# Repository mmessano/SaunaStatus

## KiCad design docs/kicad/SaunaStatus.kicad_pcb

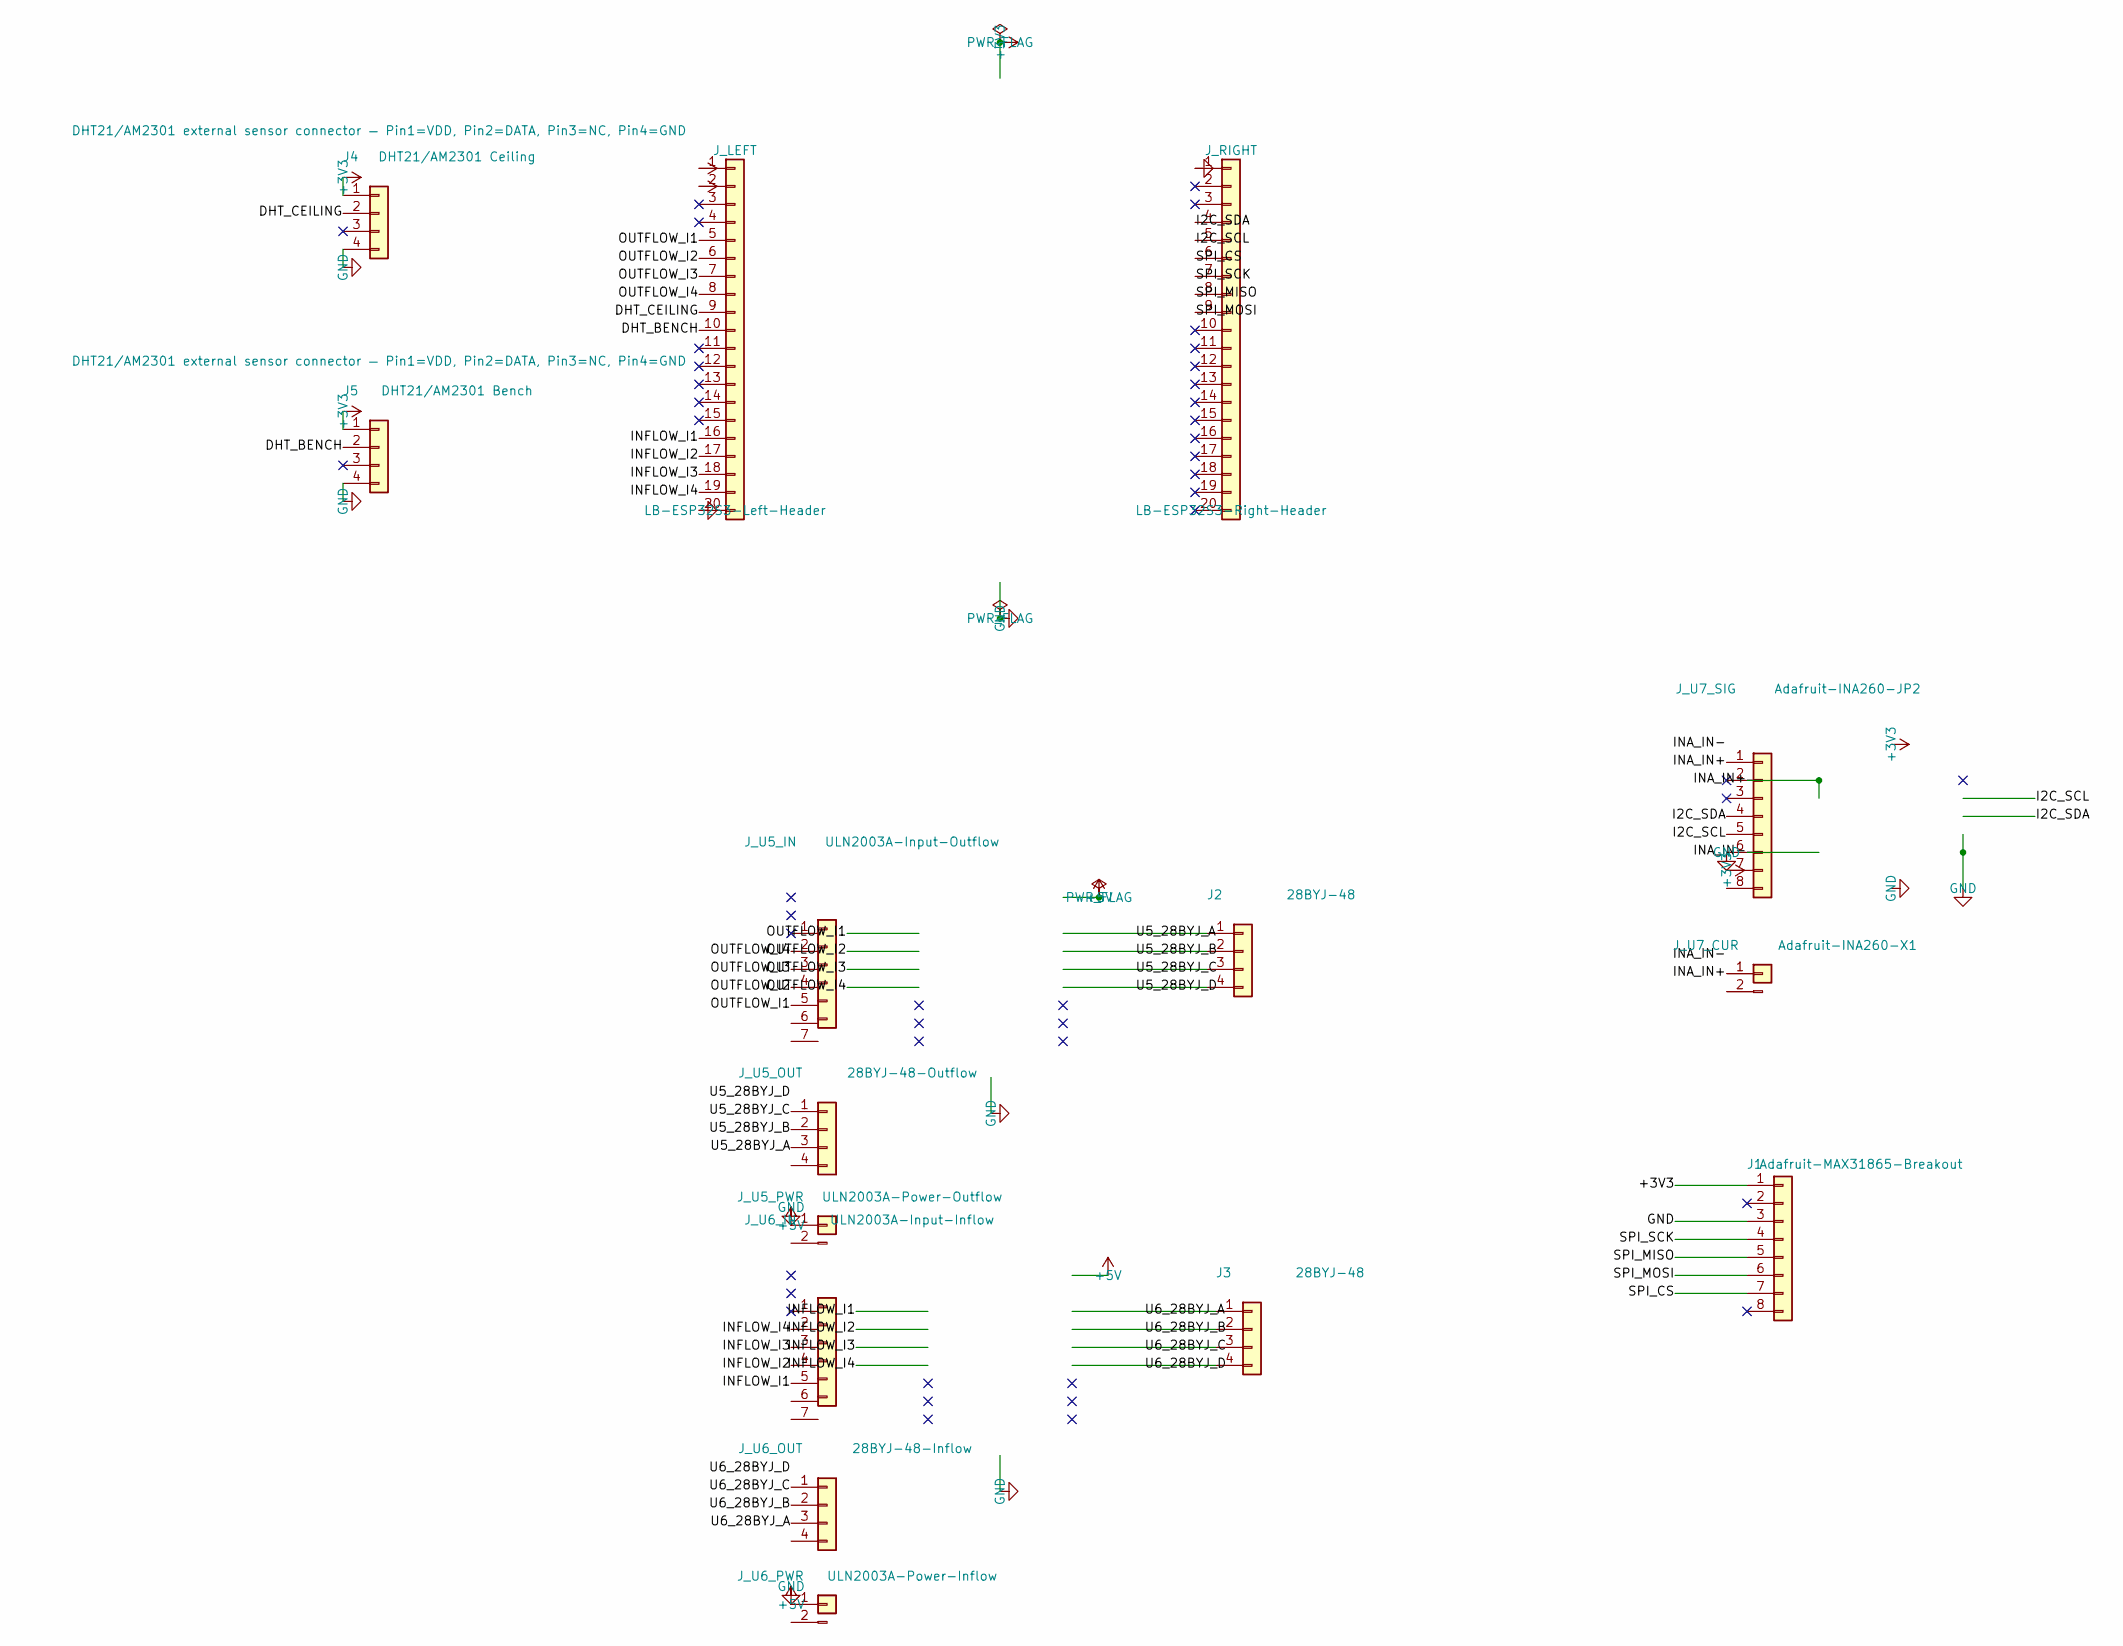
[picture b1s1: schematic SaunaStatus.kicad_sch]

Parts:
J1: Adafruit-MAX31865-Breakout; PinHeader_1x08_P2.54mm_Vertical
J2, J3: 28BYJ-48; PinHeader_1x04_P2.54mm_Vertical
J4: DHT21/AM2301 Ceiling; PinHeader_1x04_P2.54mm_Vertical
J5: DHT21/AM2301 Bench; PinHeader_1x04_P2.54mm_Vertical
J_LEFT: LB-ESP32S3-Left-Header; PinHeader_1x20_P2.54mm_Vertical
J_RIGHT: LB-ESP32S3-Right-Header; PinHeader_1x20_P2.54mm_Vertical
J_U5_IN: ULN2003A-Input-Outflow; PinHeader_1x07_P2.54mm_Vertical
J_U5_OUT: 28BYJ-48-Outflow; PinHeader_1x04_P2.54mm_Vertical
J_U5_PWR: ULN2003A-Power-Outflow; PinHeader_1x02_P2.54mm_Vertical
J_U6_IN: ULN2003A-Input-Inflow; PinHeader_1x07_P2.54mm_Vertical
J_U6_OUT: 28BYJ-48-Inflow; PinHeader_1x04_P2.54mm_Vertical
J_U6_PWR: ULN2003A-Power-Inflow; PinHeader_1x02_P2.54mm_Vertical
J_U7_CUR: Adafruit-INA260-X1; PinHeader_1x02_P2.54mm_Vertical
J_U7_SIG: Adafruit-INA260-JP2; PinHeader_1x08_P2.54mm_Vertical

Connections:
+3V3: J1.1, J4.1, J5.1, J_LEFT.1, J_LEFT.2, J_U7_SIG.7
+5V: J_U5_PWR.1, J_U6_PWR.1
/DHT_BENCH: J5.2, J_LEFT.10; also elsewhere on the board
/DHT_CEILING: J4.2, J_LEFT.9; also elsewhere on the board
/I2C_SCL: J_RIGHT.5, J_U7_SIG.5; also elsewhere on the board
/I2C_SDA: J_RIGHT.4, J_U7_SIG.4; also elsewhere on the board
/INA_IN+: J_U7_CUR.1, J_U7_SIG.1
/INFLOW_I1: J_LEFT.16, J_U6_IN.5; also elsewhere on the board
/INFLOW_I2: J_LEFT.17, J_U6_IN.4; also elsewhere on the board
/INFLOW_I3: J_LEFT.18, J_U6_IN.3; also elsewhere on the board
/INFLOW_I4: J_LEFT.19, J_U6_IN.2; also elsewhere on the board
/OUTFLOW_I1: J_LEFT.5, J_U5_IN.5; also elsewhere on the board
/OUTFLOW_I2: J_LEFT.6, J_U5_IN.4; also elsewhere on the board
/OUTFLOW_I3: J_LEFT.7, J_U5_IN.3; also elsewhere on the board
/OUTFLOW_I4: J_LEFT.8, J_U5_IN.2; also elsewhere on the board
/SPI_CS: J1.7, J_RIGHT.6; also elsewhere on the board
/SPI_MISO: J1.5, J_RIGHT.8; also elsewhere on the board
/SPI_MOSI: J1.6, J_RIGHT.9; also elsewhere on the board
/SPI_SCK: J1.4, J_RIGHT.7; also elsewhere on the board
/U5_28BYJ_A: J2.1, J_U5_OUT.3
/U5_28BYJ_B: J2.2, J_U5_OUT.2
/U5_28BYJ_C: J2.3, J_U5_OUT.1
/U5_28BYJ_D: J2.4
/U6_28BYJ_A: J3.1, J_U6_OUT.3
/U6_28BYJ_B: J3.2, J_U6_OUT.2
/U6_28BYJ_C: J3.3, J_U6_OUT.1
/U6_28BYJ_D: J3.4
GND: J1.3, J4.4, J5.4, J_LEFT.20, J_RIGHT.1, J_U7_SIG.6

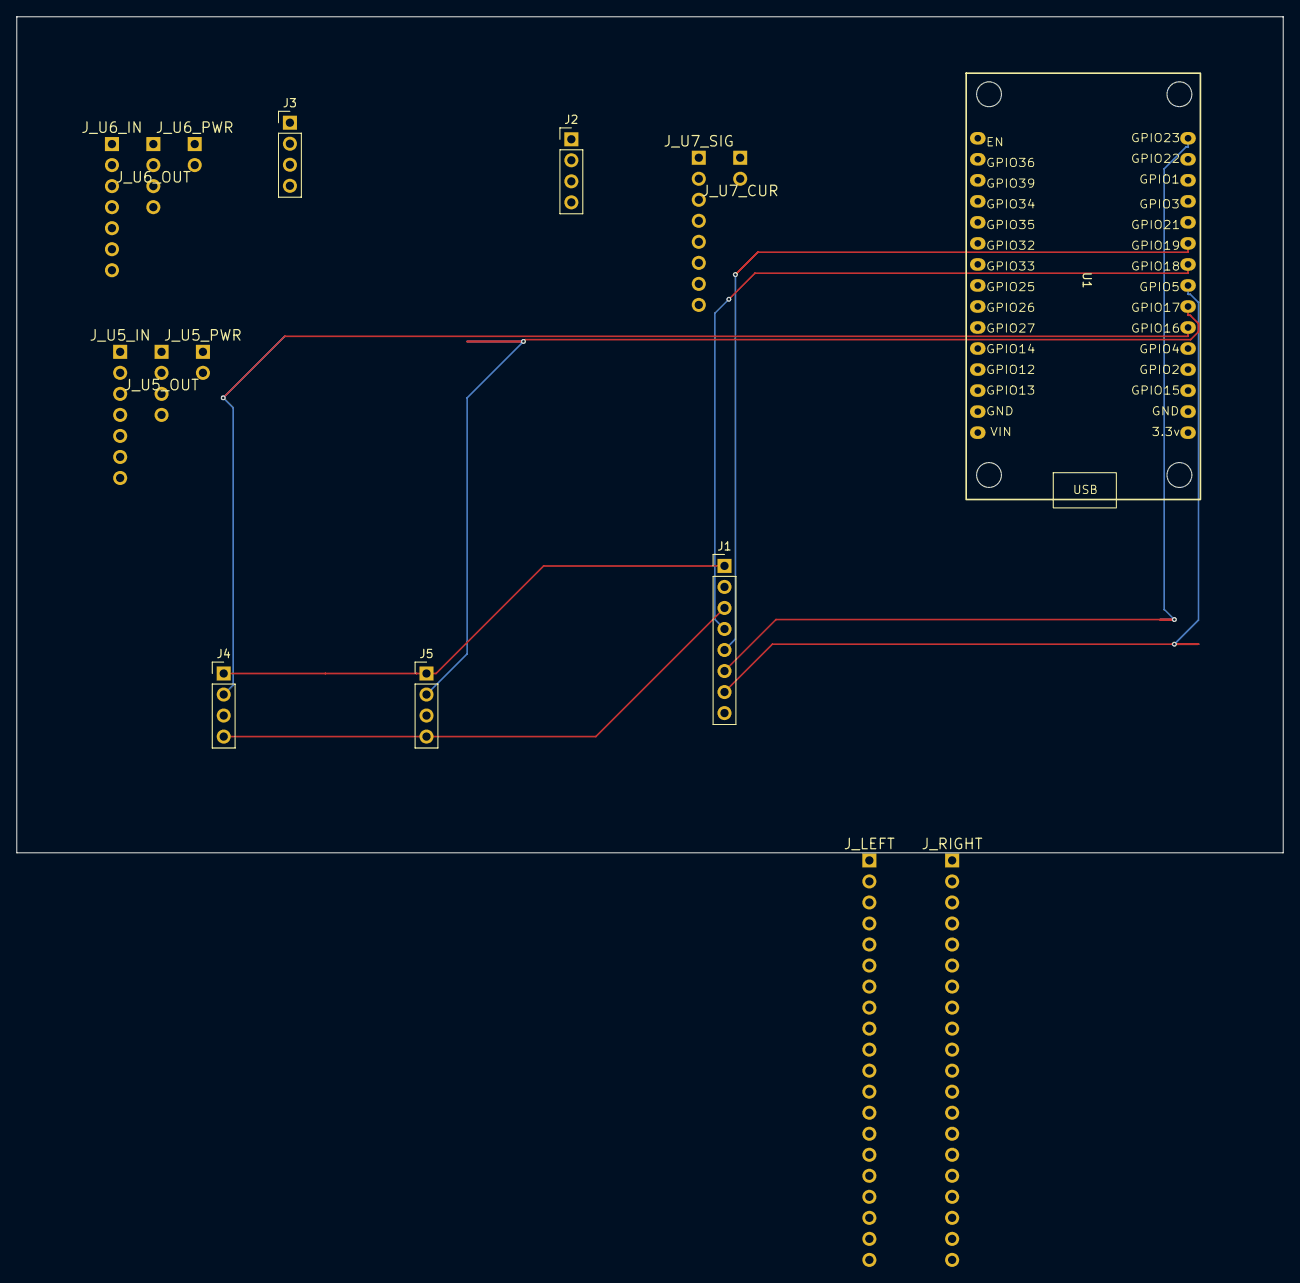
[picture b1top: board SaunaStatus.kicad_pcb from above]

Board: 2 copper layers, 153.0 x 101.0 mm, 16 parts (0 on the bottom side), 26 nets.

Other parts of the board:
U1: ESP32-DevKit-V1-DOIT; ESP32_30pin

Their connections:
/DHT_BENCH: U1.22 (IO17); also elsewhere on the board
/DHT_CEILING: U1.21 (IO16); also elsewhere on the board
/I2C_SCL: U1.13 (IO13); also elsewhere on the board
/I2C_SDA: U1.20 (IO4); also elsewhere on the board
/INFLOW_I1: U1.29 (IO22); also elsewhere on the board
/INFLOW_I2: U1.10 (IO27); also elsewhere on the board
/INFLOW_I3: U1.6 (IO32); also elsewhere on the board
/INFLOW_I4: U1.7 (IO33); also elsewhere on the board
/OUTFLOW_I1: U1.26 (IO21); also elsewhere on the board
/OUTFLOW_I2: U1.8 (IO25); also elsewhere on the board
/OUTFLOW_I3: U1.9 (IO26); also elsewhere on the board
/OUTFLOW_I4: U1.11 (IO14); also elsewhere on the board
/SPI_CS: U1.23 (IO5); also elsewhere on the board
/SPI_MISO: U1.25 (IO19); also elsewhere on the board
/SPI_MOSI: U1.30 (IO23); also elsewhere on the board
/SPI_SCK: U1.24 (IO18); also elsewhere on the board

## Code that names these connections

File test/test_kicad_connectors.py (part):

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    def test_net_i2c_scl(self, sch_text):
        """I2C_SCL must survive the INA260 (U7) → Conn_01x08 replacement.

        The INA260 breakout's SCL pin connects to I2C_SCL.  If this net
        disappears the power monitor loses its clock line.
        """
        assert "I2C_SCL" in sch_text, "Net I2C_SCL missing from schematic"
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    def test_net_i2c_sda(self, sch_text):
        """I2C_SDA must survive the INA260 (U7) → Conn_01x08 replacement.

        The INA260 breakout's SDA pin connects to I2C_SDA.  If this net
        disappears the power monitor loses its data line.
        """
        assert "I2C_SDA" in sch_text, "Net I2C_SDA missing from schematic"
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    # --- Outflow motor (U5) inputs -------------------------------------------

    def test_net_outflow_i1(self, sch_text):
        """OUTFLOW_I1 must be present (U5 input 1 from ESP32 GPIO21)."""
        assert "OUTFLOW_I1" in sch_text, "Net OUTFLOW_I1 missing from schematic"

    def test_net_outflow_i2(self, sch_text):
        """OUTFLOW_I2 must be present (U5 input 2 from ESP32 GPIO25)."""
        assert "OUTFLOW_I2" in sch_text, "Net OUTFLOW_I2 missing from schematic"

    def test_net_outflow_i3(self, sch_text):
        """OUTFLOW_I3 must be present (U5 input 3 from ESP32 GPIO26)."""
        assert "OUTFLOW_I3" in sch_text, "Net OUTFLOW_I3 missing from schematic"

    def test_net_outflow_i4(self, sch_text):
        """OUTFLOW_I4 must be present (U5 input 4 from ESP32 GPIO14)."""
        assert "OUTFLOW_I4" in sch_text, "Net OUTFLOW_I4 missing from schematic"

    # --- Outflow motor (U5) outputs ------------------------------------------
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    # --- Inflow motor (U6) inputs --------------------------------------------

    def test_net_inflow_i1(self, sch_text):
        """INFLOW_I1 must be present (U6 input 1 from ESP32 GPIO22)."""
        assert "INFLOW_I1" in sch_text, "Net INFLOW_I1 missing from schematic"

    def test_net_inflow_i2(self, sch_text):
        """INFLOW_I2 must be present (U6 input 2 from ESP32 GPIO27)."""
        assert "INFLOW_I2" in sch_text, "Net INFLOW_I2 missing from schematic"

    def test_net_inflow_i3(self, sch_text):
        """INFLOW_I3 must be present (U6 input 3 from ESP32 GPIO32)."""
        assert "INFLOW_I3" in sch_text, "Net INFLOW_I3 missing from schematic"

    def test_net_inflow_i4(self, sch_text):
        """INFLOW_I4 must be present (U6 input 4 from ESP32 GPIO33)."""
        assert "INFLOW_I4" in sch_text, "Net INFLOW_I4 missing from schematic"

    # --- Inflow motor (U6) outputs -------------------------------------------
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
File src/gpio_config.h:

// src/gpio_config.h
// GPIO pin assignments for the LB-ESP32S3-N16R8-Pinout-Modified board.
//
// All signals are grouped by physical adjacency on the board header so each
// device's wires arrive at consecutive pins — no cross-wiring required.
//
// Left header (top → bottom):  3V3, 3V3, RST, GPIO3–18 (sequential), GND
// Right header (top → bottom): GND, GPIO43, GPIO44, GPIO1, GPIO2, GPIO42–39,
//                               GPIO38–35, GPIO0, GPIO45, GPIO48, GPIO47,
//                               GPIO21, GPIO20, GPIO19, GND, GND
//
// Previous board: esp32_devkit_v1_doit (ESP32-WROOM-32, 4MB flash, no PSRAM)
// This board:     LB-ESP32S3-N16R8     (ESP32-S3, 16MB flash, 8MB OPI PSRAM)
//
// GPIO restrictions on N16R8 — DO NOT USE:
//   GPIO 0       : BOOT strapping pin (LOW → download mode)
//   GPIO 19      : USB D-  (native USB OTG)
//   GPIO 20      : USB D+  (native USB OTG)
//   GPIO 26–38   : OPI PSRAM (26–32), OPI Flash (35–37), FSPI (38) — internal
//   GPIO 43      : UART0 TX (serial monitor / upload)
//   GPIO 44      : UART0 RX (serial monitor / upload)
//   GPIO 45      : Strapping pin (VDD_SPI voltage selection)
//   GPIO 46      : Strapping pin (ROM log message enable)
//   GPIO 48      : On-board RGB LED
//
// No Arduino dependencies — this header compiles cleanly in native test builds.
#pragma once

// ─── Outflow (upper vent) stepper ─── left header, GPIO4–7 ──────────────────
// Physically adjacent pins 4–7 on the left header. IN1<IN2<IN3<IN4 matches
// CheapStepper's expected coil sequence for correct 28BYJ-48 step direction.
// Previous: IN1=GPIO21, IN2=GPIO25, IN3=GPIO26, IN4=GPIO14 (scattered)
#define OUTFLOW_IN1 4
#define OUTFLOW_IN2 5
#define OUTFLOW_IN3 6
#define OUTFLOW_IN4 7

// ─── Inflow (lower vent) stepper ─── left header, GPIO15–18 ─────────────────
// Four consecutive pins immediately after the outflow group on the left header.
// Previous: IN1=GPIO22, IN2=GPIO27, IN3=GPIO32, IN4=GPIO33 (scattered)
#define INFLOW_IN1 15
#define INFLOW_IN2 16
#define INFLOW_IN3 17
#define INFLOW_IN4 18

// ─── DHT21 temperature/humidity sensors ─── left header, GPIO8–9 ────────────
// Two adjacent pins for the two external sensor wires.
// Previous: CEILING=GPIO16, BENCH=GPIO17
#define DHTPIN_CEILING 8
#define DHTPIN_BENCH   9
#define DHTTYPE DHT21

// ─── INA260 power monitor (I2C) ─── right header, GPIO1–2 ───────────────────
// Two adjacent pins at the top of the right header (after the UART0 pair).
// Previous: SDA=GPIO4, SCL=GPIO13
#define INA260_SDA 1
#define INA260_SCL 2

// ─── MAX31865 stove thermocouple (SPI) ─── right header, GPIO39–42 ──────────
// Four consecutive right-header pins. Must call SPI.begin(SCK, MISO, MOSI)
// before stove_thermo.begin() in setup() — ESP32-S3 has no fixed default SPI pins.
// Previous: CS=GPIO5, SCK=GPIO18, MISO=GPIO19, MOSI=GPIO23 (VSPI defaults)
#define SPI_CS_PIN   42
#define SPI_SCK_PIN  41
#define SPI_MISO_PIN 40
#define SPI_MOSI_PIN 39

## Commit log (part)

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2026-03-19 Initial project commit
2026-03-19 Update CLAUDE.md and add settings.json.
2026-03-19 Add .vscode/ to .gitignore; Update claude settings.
2026-03-19 Update settings for claude.
2026-03-19 Fix UI presentation issues with sensor data.
2026-03-20 fix(auth): document authTokenEqual buffer precondition
2026-03-20 fix(auth): test_expired_slot_reclaimed_before_valid now exercises the expired-first branch
2026-03-20 fix(auth): adapter role default empty string — avoid privilege escalation on missing role field
2026-03-21 chore: begin modular refactor — baseline 113 tests passing
2026-03-21 test(web): add failing tests for buildJson() — red phase
2026-03-21 test(web): fix setUp() — reset all mutable globals between tests
2026-03-21 feat(mqtt): extract mqtt module; move savePrefs extern to globals.h
2026-03-21 refactor(main): remove extracted functions; main.cpp is now thin orchestrator
2026-03-21 chore: firmware refactor complete — 124 tests passing, firmware builds clean
2026-03-22 fix(web): replace deprecated StaticJsonDocument with JsonDocument
    Replace all StaticJsonDocument<N> usage in auth.h and web.cpp with
    JsonDocument (ArduinoJson v7 API). Also replace createNestedObject()
    with add<JsonObject>() in handleUsersGet(). Build now clean with
    zero warnings; 136 tests passing.
    Also add .claude/skills/sauna-status-patterns/SKILL.md — project
    skill extracted from git history analysis covering commit conventions,
2026-03-22 feat(kicad): replace bare IC symbols/footprints with breakout board connectors
    Replace U1 (ESP32-WROOM-32), U5/U6 (ULN2003A DIP-16), and U7 (INA260
    TSSOP-16) bare IC symbols in the schematic with connector symbols that
    match the physical breakout boards used in the build:
    - U1 → esp32_devkit_v1_doit (2×15 through-hole header)
    - U5/U6 → J_*_IN (Conn_01x07) + J_*_OUT (Conn_01x04) + J_*_PWR
    (Conn_01x02) representing ULN2003A-PCB breakout connectors
2026-03-23 fix(kicad): restore missing (symbol opening for PWR_FLAG FLG002 block
    Python schematic edit script accidentally deleted the (symbol opening
    line of the #FLG002 PWR_FLAG block while removing nearby U1 wires.
    KiCad rejected the file with 'Expecting symbol...' at line 2217.
2026-03-23 fix(kicad): add Conn_01x20 to lib_symbols; reorder symbols before sheet_instances
    Two additional issues causing ERC crash:
    1. Connector_Generic:Conn_01x20 missing from lib_symbols — KiCad embeds
    symbol geometry in the schematic; without it ERC crashes resolving
    J_LEFT/J_RIGHT pin types. Extracted from system lib and inserted.
    2. J_LEFT, J_RIGHT, and 4 power symbols were placed after sheet_instances
    and embedded_fonts sections instead of before them. Reordered to
2026-03-23 fix(kicad): rebuild schematic from clean baseline — replace U1 with J_LEFT/J_RIGHT
    Rebuilt SaunaStatus.kicad_sch from commit 2ab2052 using two-phase Python
    script to correctly replace the ESP32-DevKit-V1-DOIT (U1) with
    J_LEFT/J_RIGHT Conn_01x20 header connectors for the LB-ESP32S3-N16R8.
    Phase 1: removed U1 symbol block, 18 no-connects at U1 pin x-positions,
    16 net labels at x=177.8, and 16 wires between x=167.64 and x=177.8.
    Phase 2: inserted (before sheet_instances):
2026-03-23 fix(kicad): correct power symbol placement on J_LEFT/J_RIGHT pins
    Power symbols were off by one pin pitch (2.54mm) from where they should
    connect:
    #PWR030 (+3V3): 36.83 → 39.37 (J_LEFT pin 1)
    #PWR031 (+3V3): 39.37 → 41.91 (J_LEFT pin 2)
    #PWR032 (GND): 90.17 → 87.63 (J_LEFT pin 20)
    #PWR033 (GND): 41.91 → 39.37 (J_RIGHT pin 1)
2026-03-23 chore(claude): add sync-repos dry-run permission
2026-03-23 chore(docs): update skills, docs, and add ProS3 KiCad footprints
    - Bump sauna-status-patterns skill to v1.1.0; condense redundant
    content to point at CLAUDE.md and dedicated skills instead of
    duplicating them in the skill file
    - Update CLAUDE.md, api-reference.md, and config-reference.md
    - Update KiCad schematic generation rules
    - Add ProS3_SMD and ProS3_TH KiCad footprints for LB-ESP32S3-N16R8
2026-03-23 fix(scripts): fix test summary grep pattern and stat formatting in update-handoff.sh
2026-03-23 docs(claude): document post-commit hook installation requirement
2026-03-26 chore(claude): add plugin inspection and management permissions
2026-03-27 docs(superpowers): add implementation plan for autonomous documentation maintenance system
2026-03-27 feat(scripts): refresh-docs step 1 — delegate to update-handoff.sh
2026-03-27 feat(scripts): refresh-docs step 2 — CLAUDE.md full audit via claude --print
2026-03-27 fix(scripts): correct web.cpp comment and add DEFINES empty guard in step 2
2026-03-27 fix(scripts): use while-read loop for RECENT_PLANS to handle spaces in paths
2026-03-27 feat(scripts): refresh-docs step 4 — skill extraction via claude --print
2026-03-27 feat(scripts): refresh-docs steps 5+6 — hook verify and diff/confirm/commit
2026-03-27 chore(docs): refresh documentation and skills
2026-03-27 fix(scripts): save/restore HANDOFF.md in step 5 and close stdin for claude --print calls
2026-03-27 feat(skills): add three evolved skills from instinct clusters
    - sauna-embedded-invariants: NaN clearing, NVS isKey() guards, consumer audit (3 instincts, 92%)
    - sauna-post-edit-validation: pio run + json.tool after every edit (2 instincts, 92%)
    - sauna-tdd-workflow: red-first TDD + pio test -e native after build (2 instincts, 89%)
    Also fix hardcoded /home/mmessano/ paths in settings.local.json → ~/
2026-03-30 docs: split CLAUDE.md into docs/architecture.md and docs/testing.md
    CLAUDE.md reduced from 360 to 145 lines — behavioral rules and gotchas only.
    docs/architecture.md: source tree, module details, PID, safety systems,
    motor control, web UI, LittleFS layout, platformio.ini structure.
    docs/testing.md: test suite table (281 tests across 13 suites), undocumented
    API routes, NVS keys, and #define constants tracking list.
    CLAUDE.md updated Quick Reference table to use @docs/ references.
2026-03-30 docs: remove duplications from CLAUDE.md
    CLAUDE.md: 360 → 145 → 99 lines.
    Moved to docs/architecture.md:
    - OTA boot health implementation details
    - Authentication system implementation details (seeding, adapter flow,
    security headers, rate limit parameters, password constraints)
    Removed from CLAUDE.md (already in docs):
2026-04-01 chore: untrack workflow artifacts and local settings
    - Add .parallel-tdd/ to .gitignore (temp files from parallel TDD agent)
    - Untrack .parallel-tdd/merge-agent-prompt.txt (git rm --cached)
    - Untrack .claude/settings.local.json (already in .gitignore but was tracked)
2026-04-01 fix: use DEFAULT_STATIC_IP define in fallback path
    Fallback path when static_ip NVS value is invalid was hardcoding
    the literal string '192.168.1.200' instead of reusing the already-defined
    DEFAULT_STATIC_IP build flag, causing silent divergence if the flag
    is overridden.
2026-04-01 refactor: add PID_OUTPUT_MIN/MAX defines, replace magic 255
    QuickPID outputs 0–255; this range was hardcoded in three places:
    SetOutputLimits() calls and the output→step-count scaling divisions.
    Adding PID_OUTPUT_MIN/MAX #ifndef-guarded defines keeps all three in sync
    and allows build-flag override without touching source.
2026-04-01 refactor: add PID_AGG/CONS_KP/KI/KD defines for tuning constants
    Kp/Ki/Kd values for aggressive (4.0/0.2/1.0) and conservative
    (1.0/0.05/0.25) tuning modes were hardcoded as float literals.
    Named #ifndef-guarded defines make them overridable via build flags
    without editing source, and document the two-mode tuning scheme.
2026-04-01 refactor: add SERIAL_BAUD_RATE define
    Serial.begin(115200) was hardcoded. SERIAL_BAUD_RATE define
    documents the intent and must match monitor_speed in platformio.ini.
2026-04-01 refactor: add MQTT_TOPIC_* constants to eliminate topic string duplication
    Replace all hardcoded topic string literals in mqtt.cpp with named macros:
    MQTT_TOPIC_STATE, MQTT_TOPIC_CEILING_PID, MQTT_TOPIC_BENCH_PID,
    MQTT_TOPIC_CEILING_SP, MQTT_TOPIC_BENCH_SP. Covers mqttCallback,
    mqttPublishState, mqttPublishDiscovery (format strings via string
    literal concatenation), PUB_SW/PUB_N call sites, and subscribe calls.
2026-04-26 Add .codex to .gitignore.
2026-05-22 fix(ui): P1 safety pass — wss fallback, 401 redirect, motor label split
    C2: WebSocket URL now picks ws/wss based on location.protocol, removing
    the mixed-content failure mode under any future HTTPS front.
    H5: index.html authFetch now redirects to /auth/login on 401, matching
    config.html behavior. Previously a stale dashboard would linger after
    token expiry.
    C3: Motor card now has two labeled sub-sections — "CALIBRATE — marks
2026-05-22 test(ui): Add Playwright harness with mock ESP32 device
    Stand up tools/ui-test/ — a headless-browser test harness that lets us
    verify data/*.html changes without flashing firmware. Mirrors the pattern
    used in the Slimmer repo.
    How it works:
    - mock-server.mjs fakes every HTTP and WebSocket endpoint the dashboard,
    config portal, and login page call (auth/login, auth/status, config/get,
2026-05-22 feat(ui): H3 stateful connection indicator + H4 status threshold subtext
    H3 — Connection state no longer relies on color alone.
    - .status wrapper now carries .connecting / .ok / .err state classes
    that drive both the dot's shape AND the surrounding text color.
    - Dot shapes per state:
    connecting → outlined ring with pulse animation
    ok → filled green circle
2026-05-22 feat(ui): P3 wave 2 — themed confirm modal, refresh countdown, legend & flash polish
    M5 — Replace native confirm() with a themed modal that matches the
    dashboard palette. New themedConfirm({title, message, confirmLabel,
    requireTyping?}) returns Promise<bool>. Esc cancels, Enter confirms
    when enabled. requireTyping enables type-to-confirm: the Confirm
    button stays disabled until the user types the exact phrase
    (currently the bucket name). Used by both resetBucket (with
2026-05-23 style(ui): Center the dashboard column with max-width 1100px
    On wide monitors the dashboard previously stretched edge-to-edge and
    read as left-justified content drifting toward the viewport edge. Cap
    the body at 1100 px with margin: 0 auto so everything sits in a
    centered column, matching the pattern config.html already uses (500 px
    form). The 20 px body padding plus the inner Grid layouts keep the
    small/medium viewport experience unchanged. #authBar stays fixed to
2026-05-23 docs: Sync API + architecture + testing with shipped UI work
    verify_doc_drift.py was flagging GET /chart.umd.min.js and
    GET /chart-adapter.min.js as undocumented routes. While the docs
    were open, also bring them in line with the rest of the session's
    shipped work (web.cpp split, P1–P3 UI batches, Playwright harness).
    api-reference.md
    - New route entries for /chart.umd.min.js and /chart-adapter.min.js
2026-05-23 refactor(ui): L6 + L7 — single login UI, addEventListener for all handlers
    L7 — Removed the inline #login-panel overlay from data/index.html. The
    dashboard is now strictly the authenticated view: on DOMContentLoaded
    it checks for a token, fetches /auth/status, and either reveals the
    chrome (success) or redirects to /auth/login (no token or 401). The
    overlay had been a redundant second login UI since C1; with the visual
    theme unified earlier, this finishes the collapse. The body now starts
